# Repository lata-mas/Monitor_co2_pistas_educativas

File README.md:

# Monitor de CO2 con sensores NDIR intercambiables para evaluar la ventilación natural

En este repositorio se encuentran los archivos necesarios para replicar el monitor de CO2 desarrollado en el Instituto de Energías Renovables de la UNAM, ubicado en Temixco, Morelos, México.

Los archivos para el PCB se encuentran en el folder **electric_design**. Los archivos KiCAD del esquema del PCB y el diagrama eléctrico se encuentran en el folder **pcb_src**. Los archivos para maquinar o cortar por láser el PCB se encuentran en el folder **pcb_gerber**. El diagrama eléctrico en formato PDF se encuentra en el folder **pcb_pdf**. Las plantillas para producir el PCB por impresión de pantalla en formato JPG se encuentran en el folder **pcb_jpg**. Adicionalmente, renders tridimensionales del PCB con las partes del monitor se encuentran en el folder **pcb_view3D**. Los archivos para producir la carcasa del monitor de CO2 se encuentran en el folder **hardcase_pdf**. Los archivos FreeCAD se encuentran en el folder **cad**, junto con archivos en PDF para calcar en el folder **hardcase_pdf**, y también archivos en formato STL y DXF en el folder **hardcase_printable**.

El programa, código fuente y binario, se encuentran en el folder **software**. En el folder **notebook** se encuentran libretas de Jupyter con los datos de la calibración hecha y la campaña experimental, los datos se encuentran en el folder **dat**.

# Lista de componentes
| Designador  | Componente                      | Cantidad | Costo (MXN) | Fuente de materiales |
|-------------|---------------------------------|----------|-------------|----------------------|
| ESP8266     | NodeMCU V3.0 Lolin              | 1        | 159.0       | [Steren](https://www.steren.com.mx/placa-de-desarrollo-nodemcu-esp8266.html) |
| Sensor CO2  | S8LP                            | 1        | 800.0       | [Digikey](https://www.digikey.com.mx/es/products/detail/senseair/004-0-0053/10416532) |
| Sensor CO2  | SEN0220                         | 1        | 1600.0      | [DFROBOT](https://www.dfrobot.com/index.php?route=product/product&product_id=1565) |
| Sensor CO2  | SCD30                           | 1        | 1067.0      | [DigiKey](https://www.digikey.com.mx/es/products/detail/sensirion-ag/SCD30/8445334) |
| Pantalla    | Pantalla de 4 dígitos           | 1        | 112.0       | [Seeed Studio](https://www.seeedstudio.com/Grove-4-Digit-Display.html?queryID=a52cccea41a634e8bc10114075018055&objectID=1651&indexName=bazaar_retailer_products) |
| LED         | LED RGB                         | 1        | 4.3         | [Seeed Studio](https://www.seeedstudio.com/5mm-Triple-Output-LED-RGB-Common-cathode-20-PC-p-623.html?queryID=996fc5e5da5e1e2ef55538094fc749c5&objectID=1920&indexName=bazaar_retailer_products) |
| BUZZER      | Zumbador activo                 | 1        | 27.7        | [Seeed Studio](https://www.seeedstudio.com/Grove-Buzzer.html?queryID=762ee5a017832256c2a6a486656facf6&objectID=1805&indexName=bazaar_retailer_products) |
| microUSB    | Adaptador microUSB              | 1        | 7.0         | [UElectronics](https://uelectronics.com/producto/adaptador-micro-usb-tipo-b-hembra-a-dip-pcb-5-pines/) |
| Botón       | Botón pulsador                  | 1        | 27.7        | [Newark](https://www.newark.com/philmore/30-10062/product-range/dp/43W7727?st=button) |
| Batería     | Banco de energía 2500 mAh       | 1        | 200.0       | [Newark](https://www.newark.com/multicomp/mc011332/power-bank-5-2ah-5vdc/dp/94AC6834?st=power%20bank) |
| R1          | Resistencia de 10 kOhm          | 1        | 2.5         | [Newark](https://www.newark.com/arcol/mra0207-10k-b-15ppm-ta/res-10k-0-10-250mw-axial/dp/79Y4556?st=resistor%2010kohm) |
| R2          | Resistencia de 220 Ohm          | 3        | 2.5         | [Newark](https://www.newark.com/multicomp-pro/mccfr0w4j0221a50/carbon-film-resistor-220-ohm-250mw/dp/58K5029?st=resistor%20220%20ohm) |
| Grove       | Cable groove                    | 1        | 2.5         | [Seeed Studio](https://www.seeedstudio.com/Grove-Universal-4-Pin-Buckled-5cm-Cable-5-PCs-Pack.html?queryID=5db340ba008fd0a5fd1f440a6d09659c&objectID=1701&indexName=bazaar_retailer_products) |
| Terminal    | Conector vertical de 4 pines GROVE 2mm | 1  | 2.5  | [Digikey](https://www.digikey.com.mx/en/products/detail/seeed-technology-co-ltd/110990030/5482560) |
| Pines       | 40 pines hembra                 | 2        | 6.7         | [Seeed Studio](https://www.seeedstudio.com/2-54mm-pitch-pin-headers-Female-40pin-in-1-line-p-16.html?indexName=bazaar_retailer_products&objectID=2093&queryID=3d723c52f9b58905e53b48e95182a7c6) |
| Tornillos   | Tornillos M3 x 60 mm            | 4        | 5.0         | [Amazon](https://www.amazon.com.mx/gp/product/B08XB8S55X/ref=ppx_yo_dt_b_search_asin_title?ie=UTF8&th=1) |
| Tuercas     | Tuercas hexagonales M3-0.5 mm   | 4        | 1.0         | [Amazon](https://www.amazon.com.mx/gp/product/B07ZFFFRJ5/ref=ppx_yo_dt_b_search_asin_title?ie=UTF8&th=1) |
| Popote      | Popote rígido de plástico       | 2        | 3.4         | [Amazon](https://www.amazon.com.mx/Pajitas-Repuesto-Pl%C3%A1stico-Reutilizables-Pinceles/dp/B0925H4F6R/ref=sr_1_18?__mk_es_MX=%C3%85M%C3%85%C5%BD%C3%95%C3%91&crid=IM4WCLYX9S0K&keywords=popote+rigido&qid=1693848668&sprefix=popote+rigido%2Caps%2C150&sr=8-18&ufe=app_do%3Aamzn1.fos.4e545b5e-1d45-498b-8193-a253464ffa471) |
| Cable       | Cable jumper o 22-26 AWG 6 cm   | 2        | 1.8         | [Adafruit](https://www.adafruit.com/product/794) |

# Instrucciones de armado

El proceso de construcción se divide en cinco etapas. La primera etapa describe el ensamblaje del hardware para el monitor de CO2. La segunda etapa detalla la configuración y el procedimiento de carga del firmware para el ESP8266. En la tercera etapa se realiza una prueba de ensamblaje y en la cuarta etapa se lleva a cabo la configuración para la plataforma IoT. La quinta y última etapa implica el ensamblaje de la carcasa y la conexión de la batería USB si es necesario. Es importante destacar que el monitor de CO2 puede construirse y probarse en ausencia de los sensores de CO2, lo que permite adaptarse a posibles demoras en la entrega de componentes en regiones como México.

### Ensamblaje del monitor de CO2

Los siguientes pasos deben llevarse a cabo una vez que el usuario esté listo para construir el monitor de CO2, considerando que se puede probar y configurar aunque no haya un sensor de CO2 en el momento de la construcción, definiendo un sensor ficticio.

1. La PCB es de doble cara y puede producirse mediante serigrafía o mecanizado. Una de las caras tiene impresa la posición de las resistencias, sensores, led, etc., que se llamará cara frontal y el lado sin etiquetar cara trasera. Ambos lados de la PCB se muestran en la Figura 1a) cara frontal y 1b) cara trasera.
2. Soldar dos cables puente (6 cm de largo) al botón pulsador.
3. Soldar los siguientes componentes en la cara frontal. Cuatro resistencias, que están marcadas en la PCB como R1 para la resistencia de 10 $kOhm$ y R2, R3 y R4 son resistencias de 220 $Ohm$. Soldar dos líneas de quince pines hembra para el ESP8266. Soldar un conector hembra de cuatro pines para el LED. Para el botón, introducir los cables del botón en esta cara, por lo que la soldadura debería estar en la cara trasera. Insertar el conector vertical grove y soldar. En este punto, la PCB debería parecerse a la Figura 1c).
4. En la cara trasera, soldar lo siguiente: Soldar el adaptador MicroUSB y el conector hembra de tres pines para el zumbador, el conector hembra para este último debe estar doblado.
5. Si se usa S8LP, soldar dos líneas de conector hembra de seis pines en la cara trasera. En este punto, la cara trasera de la PCB debería parecerse a la Figura 1d). Luego soldar dos líneas de seis pines al sensor CO2 S8LP y enchufarlo en la PCB como se muestra en la Figura 2a).
6. Si se usa SCD30 o SEN0220, soldar una línea de conector hembra de cuatro pines en la cara trasera y, dependiendo del sensor, conectar como se muestra en la Figura 2b) para SCD30 y como se muestra en la Figura 2c) para SEN0220.
7. Enchufar el cable rojo del LED RGB apuntando al borde de la PCB en la cara frontal.
8. Enchufar la pantalla de 4 dígitos con un cable universal de cuatro pines con hebilla.
9. Enchufar el zumbador en el conector hembra de tres pines doblado.
10. Enchufar el ESP8266 con conexión microUSB alineada con el borde de la PCB.
<table>
  <tr>
    <td>
      <figure>
        
        <figcaption>a)</figcaption>
      </figure>
    </td>
    <td>
      <figure>
        
        <figcaption>b) </figcaption>
      </figure>
    </td>
  </tr>
  <tr>
    <td>
      <figure>
        
        <figcaption>c) </figcaption>
      </figure>
    </td>
    <td>
      <figure>
        
        <figcaption>d) </figcaption>
      </figure>
    </td>
  </tr>
</table>

**Figura 1**: a) Cara frontal y b) cara trasera de la PCB para el monitor de CO2 sin componentes. Tras soldar los componentes c) cara frontal y d) cara trasera de la PCB. La cara frontal tiene etiquetas para los componentes.

<table>
  <tr>
    <td style="text-align: center;">
      <figure>
        
        <figcaption>a) S8LP</figcaption>
      </figure>
    </td>
    <td style="text-align: center;">
      <figure>
        
        <figcaption>b) SCD30</figcaption>
      </figure>
    </td>
    <td style="text-align: center;">
      <figure>
        
        <figcaption>c) SEN0220</figcaption>
      </figure>
    </td>
  </tr>
</table>

<figcaption>**Figura 2**: a) S8LP, b) SCD30, y c) SEN0220 sensores conectados en la cara trasera.</figcaption>

### Configuración y carga del firmware en el ESP8266

Antes de cargar el firmware en el ESP8266, en el archivo .ino, localiza la línea `#define S8LP` y reemplaza `S8LP` con el sensor de CO2 que hayas elegido. Las opciones disponibles son `DUMMY, SEN0220` y `SCD30`. Vale la pena mencionar que la opción `DUMMY` se utiliza cuando el sensor seleccionado no está disponible. Esta opción genera datos simulados, permitiendo evaluaciones preliminares del hardware.

Adicionalmente, en las líneas donde se define:

```
#define CO2_MIN 400
#define CO2_MID 600
#define CO2_MAX 700
```

tienes la opción de configurar los colores verde, amarillo y rojo, respectivamente, que también corresponden a la alarma audible.

En el archivo `arduino_secrets.h`, los usuarios deben especificar la URL de la plataforma IoT ThingsBoard. Además, el ESP8266 establece un servicio web específico para configurar la red WiFi a la que se unirá y el token del dispositivo donde el monitor de CO2 publicará sus datos. El nombre de usuario y contraseña del administrador pueden ajustarse en este archivo o mantenerse como están.

Una vez que todos los cambios necesarios estén hechos, el archivo .ino puede cargarse en el ESP8266 usando el Arduino IDE. Cuando se configura un gran conjunto de monitores de CO2, se recomienda exportar el archivo como un archivo binario. Para hacer esto, una vez abierto el archivo .ino y compilado para verificar errores, el usuario debe ir a Sketch, Export compiled binary y el archivo binario puede cargarse en diferentes monitores de CO2. En la carpeta /software/build del repositorio se puede encontrar el archivo binario que usamos para configurar los monitores de CO2 y un script bash, `foo.sh`, como referencia para cargar el binario usando esptool.

### Prueba de ensamblaje

Al encender el Monitor de CO2, este verificará si el zumbador y el LED RGB están funcionando correctamente. Si ambos funcionan bien, el zumbador emitirá un sonido y el LED RGB mostrará los colores rojo, verde y azul antes de comenzar a funcionar.

### Configuración para la plataforma IoT

Una vez cargado el firmware en el ESP8266 y encendido por primera vez, el monitor de CO2 establece automáticamente un punto de acceso denominado `monitorCO2-XXXXXXXXX` donde las `X` se reemplazan con los últimos nueve dígitos de la dirección MAC de cada ESP8266. Para configurar el token necesario y la información de WiFi, haz lo siguiente:

1. Conéctate a la red WiFi del monitor de CO2 llamada `monitorCO2-XXXXXXXXX` desde un computador cercano.
2. Abre un navegador y navega a `http://192.168.4.1`, donde te llevará a una interfaz de configuración.
3. Inicia sesión utilizando las credenciales predeterminadas: nombre de usuario `admin` y contraseña `password`. Estos corresponden a las constantes `SECRET_WWW_USERNAME` y `SECRET_WWW_PASSWORD` en el archivo .ino del firmware. A menos que el código haya sido modificado, estas serán las credenciales predeterminadas.
4. Luego se te solicitará que ingreses los detalles de la red WiFi que el ESP8266 utilizará para conectarse a Internet junto con su contraseña, también se te pedirá el token del dispositivo.
5. Después de proporcionar esta información, el monitor de CO2 almacenará los datos y desactivará su función de punto de acceso.
6. Reinicia el ESP8266.

Si decides no completar esta configuración, el monitor de CO2 seguirá siendo completamente operativo para mediciones pero no enviará datos a la plataforma IoT y el punto de acceso estará disponible hasta que se realice la configuración.

### Carcasa para el monitor de CO2 y batería

La carcasa del Monitor de CO2 consiste en dos láminas rígidas con recortes para la pantalla, el led y para el botón. Se ensambla con cuatro tornillos, tuercas y dos popotes cortados en ocho piezas (2.5 cm cada pieza) que se utilizan como separadores. Antes de ensamblar la carcasa, el monitor de CO2 debe parecerse a lo mostrado en la Figura 3 a) la cara frontal y b) la trasera usando el S8LP. En la Figura 4 a) se muestran las láminas rígidas para la carcasa con los recortes para el sonido, ranuras, pantalla, botón, led y tornillos para el ensamblaje. La pantalla se asegura a una de las láminas rígidas usando 2 tornillos que generalmente se incluyen con la pantalla. En la misma lámina, hay un orificio donde encaja el LED, en caso de usar tableros opacos. También tiene 4 orificios por los cuales pasarán los tornillos. Esta lámina corresponde a la cara frontal de la PCB. La otra lámina de la carcasa tiene un recorte para asegurar el botón y ranuras para asegurar una ventilación adecuada para el sensor de CO2.

Finalmente, el monitor de CO2 ensamblado con láminas transparentes como carcasa y con una batería USB adjunta se muestra en la Figura 4 b).

**Figura 3**: a) Cara frontal y b) cara trasera de la PCB con todos los elementos soldados y enchufados.

**Figura 4**: a) Láminas rígidas con recortes para la carcasa, tornillos y popotes rígidos y b) Monitor de CO2 completamente ensamblado y funcionando, alimentado con una batería USB.

### Instrucciones de operación

Una vez que el monitor de CO2 está ensamblado y configurado, puede ser encendido utilizando el cable microUSB. Al activarse, el monitor comienza a medir las concentraciones de CO2, mostrando el promedio móvil de un minuto en su pantalla de 7 segmentos. Las alarmas visuales y sonoras preconfiguradas alertarán a los usuarios cuando sea necesario ventilar (indicado por una luz amarilla o dos pitidos) o si se recomienda evacuar el espacio (señalado por una luz roja y tres pitidos).

La alarma audible del Monitor de CO2 está diseñada para activarse cuando las concentraciones de CO2 alcanzan o superan las 600 ppm. Específicamente, para niveles entre 600 y 699 ppm, la alarma produce dos pulsos cada 20 segundos. Para concentraciones de 700 ppm o más, emite tres pulsos en el mismo intervalo. Esta característica auditiva es especialmente beneficiosa para usuarios con discapacidad visual que podrían tener dificultades con el sistema de colores o la lectura de la pantalla. Para desactivar temporalmente la alarma audible, presiona y mantén presionado el botón durante 20 segundos después del pitido. La alarma se reactivate una vez que las concentraciones de CO2 vuelvan al rango seguro de 400-599 ppm, asegurando alertas renovadas si los niveles exceden las 600 ppm. Si se prefiere, el zumbador puede ser excluido o desmontado del diseño sin afectar las funciones del monitor.

Los tres sensores seleccionados cuentan con un mecanismo de autocalibración que asume una exposición periódica al aire fresco (aproximadamente 400 ppm de CO2) durante la operación. Para una precisión de calibración óptima, los sensores deben experimentar exposición al aire fresco. Sin embargo, en entornos con concentraciones de CO2 consistentemente elevadas, la calibración manual puede ser más apropiada, ya que la falta prolongada de exposición a niveles ambientales puede resultar en desviaciones de calibración.

Si el Monitor de CO2 encuentra algún problema, mostrará uno de los siguientes códigos de error en su pantalla:
- F000: Imposible conectar al WiFi.
- E000: Falla en la medición del sensor de CO2.
- E001: Falla en la inicialización del sensor de CO2.
- E002: Falla en la modificación del intervalo de medición.
- E003: Falla en el comando de autocalibración.

Los mensajes de error E002 y E003 son exclusivos del sensor SCD30 y podrían aparecer durante su modo de autocalibración. Este modo puede ser activado dentro del código de Arduino a través de la función `InitSensor()`.

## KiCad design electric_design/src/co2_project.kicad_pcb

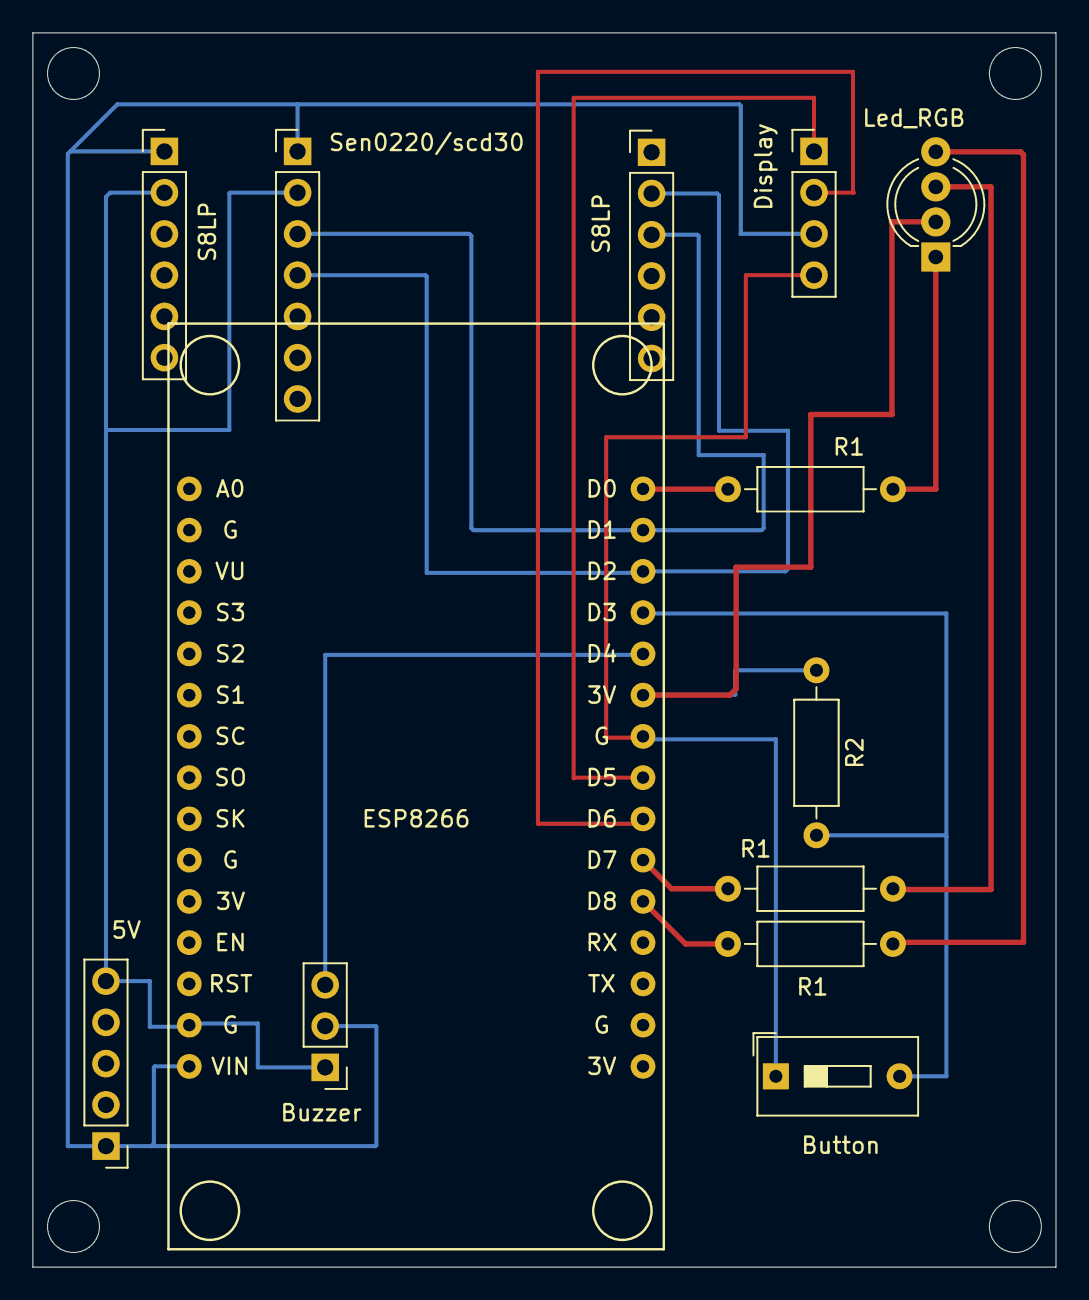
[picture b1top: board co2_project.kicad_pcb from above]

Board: 2 copper layers, 63.0 x 76.0 mm, 13 parts (0 on the bottom side), 16 nets.

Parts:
5V: 5v; PinHeader_1x05_P2.54mm_Vertical
Button: Button; SW_DIP_SPSTx01_Slide_9.78x4.72mm_W7.62mm_P2.54mm
Buzzer: Buzzer_activo; PinHeader_1x03_P2.54mm_Vertical
Display: Display; PinHeader_1x04_P2.54mm_Vertical
ESP8266: NodeMCU_1.0_(ESP-12E); NodeMCU-LoLinV3
Led_RGB: LED_RGB; LED_D5.0mm-4_RGB_Wide_Pins
R1, R1#2, R1#3: 220; R_Axial_DIN0207_L6.3mm_D2.5mm_P10.16mm_Horizontal
R2: 10k; R_Axial_DIN0207_L6.3mm_D2.5mm_P10.16mm_Horizontal
S8LP: s8; PinHeader_1x06_P2.54mm_Vertical
S8LP#2: lp; PinHeader_1x06_P2.54mm_Vertical
Sen0220/scd30: sen0220_scd30; PinHeader_1x07_P2.54mm_Vertical

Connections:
unnamed: Led_RGB.1, R1#3.2
unnamed: ESP8266.25, Led_RGB.2, R2.1
unnamed: Led_RGB.3, R1#2.2
unnamed: Led_RGB.4, R1.2
unnamed: 5V.1, Buzzer.2, Display.3, ESP8266.15, S8LP#2.1, Sen0220/scd30.1
unnamed: 5V.5, Buzzer.1, ESP8266.14, S8LP#2.2, Sen0220/scd30.2
unnamed: ESP8266.20, R1.1
unnamed: ESP8266.21, R1#2.1
unnamed: ESP8266.30, R1#3.1
unnamed: Button.2, ESP8266.27, R2.2
unnamed: Button.1, Display.4, ESP8266.24
unnamed: Buzzer.3, ESP8266.26
unnamed: Display.2, ESP8266.22
unnamed: Display.1, ESP8266.23
unnamed: ESP8266.28, S8LP.2, Sen0220/scd30.4
unnamed: ESP8266.29, S8LP.3, Sen0220/scd30.3

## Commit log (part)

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2021-06-25 detalles
2021-06-25 integracion de seaborn
2021-06-25 integracion de seaborn y correcciones de estilo
2021-06-25 boxplot showmean=true
2021-06-29 mensaje
2021-06-30 actualizacion prueba 002
2021-06-30 agregue datos de sensores thingsboard
2021-06-30 agregue nuevamente datos de sensores thingsboard
2021-07-01 prueba de concentraciones
2021-07-04 respaldo
2021-07-05 Add files via upload
    agregue datos del fluke prueba fin de semana
2021-07-06 agregue datos fluke prueba ventilador
2021-07-06 actualiza
2021-07-07 caja hermetica con ventilador
2021-07-07 Universal Shield v1.1
    Damn! SEN0220 connects RX with RX and TX with TX, instead of common
    sense UART connections RX-TX / TX-RX.
    SEN0220 is used as reference sensor, so changed to match SEN0220
    connector.
    Other UART sensor must follow RX-TX / TX-RX convention.
2021-07-07 Universal Code for Arduino Uno WiFi Rev. 2
    Just define your sensor with:
    Supported sensors:
    * DUMMY (test purposes)
    * SEN0219 (deprecated)
    * MH_Z14A
    * SEN0220
2021-07-07 Added POST_INTERVAL_MS
    Defines the post interval in milliseconds to MQTT broker.
    Default: one read/post every 60 seconds.
2021-07-08 Fixed mistaken CREDENTIALS in arduino_secrets.h
    Vaya, por fin regresó el iZZi. Corrigiendo las CREDENCIALES
    de acceso al thingsboard.
2021-07-12 Added suport for scd30. Thank you very much, Lady Ada.
    There is a library from AdaFruit for sensor scd30.
2021-07-16 Added support for ESP32 based dev boards
    Compiled for Adafruit ESP32 Feather and LOLIN ESP32 dev board
2021-07-19 documentacion scd30
2021-07-21 pruebas con scd30
2021-07-22 repo
2021-07-23 agruegue datos Fluke de la prueba 700 y 800 ppm
2021-07-23 primer resultado scd30
2021-07-24 Added co2scd30 +WiFi +(oled|epd) +lowpower
    For Arduino MKR1000, MKR1010 and Nano33 IoT
    Supports SSD1306 128x64 mono OLED
    Preliminary support for SSD1681 200x200 mono EPD
2021-07-26 agregue nuevamente pruebas del dia 23/07/2021
2021-07-26 analisis funciones
2021-07-26 libreta automatizada concentraciones
2021-07-27 co2 520, 625, 750, 800 ppm
2021-07-27 update imac
2021-07-27 actualiza orden
2021-07-27 normalizar libretas
2021-07-28 integrar resultados
2021-07-28 resultados, observaciones
2021-07-30 imagen
2021-07-30 tabla
2021-07-30 tabla formateada
2021-07-30 referencias
2021-07-30 sensores
2021-07-30 contenido
2021-07-30 agregue datos del fluke y disp nuevos prueba 800
2021-08-04 libreta induccion
2021-08-04 documentacion
2021-08-05 Preliminar WiFi recovery method
    Try to recover WiFi connection when POST statuscode != 200
    If connection can't be recovered, starting waiting one second.
    Every iteration doubles the wait time, until 128 seconds. Then
    restart with one second wait until connection is recovered.
    Builtin LED flashes fast while waiting for WiFi connection.
    No sensor data is read while recovering connection.
2021-08-05 No keep waiting for WiFi recovery but display sensor value
    Modified: not wait wifi connection, try once and return.
    Read/Display sensor, then try to POST to network, if
    statuscode != 200 try once reconnect WiFi.
2021-08-05 Added ESP8266 pin layout
    Default pinout for UART(13,15) & I2C(4,5), no need to rewrite code
    Display(CLK/DIO)=(12,14) moved from(6,7)
2021-08-05 Sensor scd30 with 128x64 OLED display
    Updated latest WiFi recovery method from co2-all-sensors
    Added IER-UNAM splash screen
2021-08-05 The sandbox
    Added splash.h
    Added sandbox, por si quieren compartir algo, eventualmente se borrará}
    del repositorio cuando una vez que esté terminado.
2021-08-05 Fixed list of sensors
    Just fixed list of sensors to include:
    * DUMMY
    * SEN0219
    * SEN0220
    * MH-Z14A
    * T3022
2021-08-05 Documentation for every sensor tested so far now
    PDF documentation from manufacturers:
    * SEN0219 aka Winsen MH-Z14A
    * SEN0220 aka Winsen MH-Z16
    * T3022 aka Telaire T67xx
    * S8LP aka Sensair S8 Low Power
    * SCD30 aka Sensirion SCD30 Sensor Module
2021-08-06 Added support for 8-bits AVR ATmega32u4 boards
    Tested with Arduino Leonardo. It should work with Arduino Micro
    and other 32u4 boards with Serial1
2021-08-07 Probando las capacidades del ESP8266
    Simple "multi-tasking" program
2021-08-08 Preliminar: soporte para el scd30
    Algoritmo loop()
    Si hay datos disponibles del sensor
    Leer Sensor
    Mostrar co2ppm en pantalla de segmentos
    Si es tiempo de postear
    Preparar payload
2021-08-08 Ticker library para crear dos cauces
    Se intentó utilizar la biblioteca Ticker para crear dos cauces:
    1 cauce para leer el sensor cada 2 segundos
    2 cauce para postear al thingsboard
    El programa revienta cuando trata de postear y aún no está establecida
    la comunicación. En realidad, nunca pudo establecer la comunicación, así
    que siempre reventó.
2021-08-09 s/ArduinoHttpClient/ESP8266HTTPClient/
    Se cambió la biblioteca ArduinoHttpClient por ESP8266HTTPClient
    Aunque ya no revienta, sigue sin postear, error=-1:connection
    failed
    ¿Será que no le gusta postear dentro del ticker?
2021-08-09 Preliminar servidor de web para configuración en línea
    Aún no decidimos si va a ser necesario hacer una configuración en línea
    pero por lo pronto tiene un servidor de dos páginas, que en realidad no
    hace gran cosa-.
2021-08-10 Prueba final del ticker: con soporte para los tres sensores
    Esta versión funciona lo suficientemente bien como para promoverla
    al directorio sketchbook con nombre (final) monitorCO2.ino
2021-08-10 monitorCO2: primera versión
    Optimizada con las bibliotecas especializadas para el ESP8266
    Utiliza la biblioteca Ticker para el control de la lectura de datos
    y para el POST en el thingsboard
    Soporta los sensores: sen0220, s8lp y scd30
    Soporte preliminar para servidor de web, con autentificación básica
    (usuario/contraseña) para configuración en línea.
2021-08-10 agregue scr s8lp con codigo de rgb y buzzer
2021-08-10 Algunos ajustes menores
    Utilizando como período de lectura MEASUREMENT_INTERVAL*1024ms
2021-08-10 D1/D2 (5/4) para I2C y para SoftwareSerial
    Esto nos deja libres los pines 12-15 para el LED RGB y para el Zumbador.
    Y tal vez reutilizar el botón FLASH en el pin 0
2021-08-10 agregue pin layout jpg
2021-08-10 monitorCO2 pin reference 2021-08-10-000
    Primera revisión del monitorCO2 con la referencia de pines del
    2021-08-10-001
    Creo que hay un conflicto con LED_BUILTIN y BUZZER
    En todo este tiempo LED_BUILTIN parpadea rápidamente si hay algún
    problema, y lentamente en operación normal.
2021-08-10 Ultima versión con LED_BUILDIN como testigo de operación.
    No modo: no alcanzan los pines. A quitar el uso del LED_BUILTIN como
    testigo de operación.
2021-08-10 Prueba del Buzzer con la biblioteca Ticker
    Para no bloquear el monitorCO2 con delays
2021-08-10 Se ha eliminado el uso del LED_BUILTIN como testigo de operación
    En algunos lugares he agregado mostrar los códigos de error en el
    display
2021-08-11 Fixed chkwifi() report on display
    Faster report chkwifi() on display
2021-08-11 chkwifi() now reports WiFi.status() on display
    From wl_definitions.h
    0xf000 WL_IDLE_STATUS
    0xf001 WL_NO_SSID_AVAIL
    0xf002 WL_SCAN_COMPLETED
    0xf003 WL_CONNECTED
    0xf004 WL_CONNECT_FAILED
2021-08-11 co2ppm = cma.avg()
    Unificando el valor co2ppm al promedio, se utiliza para el display,
    el semáforo, la alarma y el POST.
2021-08-11 Added cma.h & cma.cpp
    I forgot to add these files
2021-08-12 Added CurieEddystoneURL
    Eddystone(TM) URL permite publicar un URL en el sistema BLE.
    Un teléfono inteligente puede detectar la baliza y abrir el URL.
2021-08-12 agregue esquematico y vista proto de ESP8266_CO2
2021-08-12 agregue correción del esquematico
2021-08-12 co2_fritzing
2021-08-12 agregue correcion de esquematico CO2
2021-08-13 hize una pequeña correcion en el esquematico
2021-08-13 test-eeprom
    Un poco más complicado de lo que yo esperaba, pero ya se puede
    escribir/leer datos a la EEPROM
    Aunque de momento tal parece que sólo necesitamos el ACCESS_TOKEN
    de una vez aproveché para agregar WIFI_SSID y WIFI_PASS
2021-08-13 agregue correcion de esquematico
2021-08-18 agregue archivos gerber y fritzing del pcb
2021-08-21 Prueba de concepto WIFI-AP -> WIFI-STA
    Si el EEPROM está vacío arranca como ACCESS_POINT con SSID=monitorCO2-MAC-ADDRESS
    Si el EEPROM tiene datos los utiliza para conectarse a la red indicada
    Se configura un WebServer con tres URI iniciales:
    / RootPage: debe presentar un formulario pidiendo los datos y apuntando a /commit
    /commit recibe el formulario, copia los datos y escribe la EEPROM
    /clear sirve para borrar la EEPROM mientras hacemos pruebas
2021-08-21 Intento de poner un BEACON con el URL del Sensor, pero no sirve sin instalar una apĺicación
    Aunque el BEACON funciona, requiere instalar una aplicación, así que realmente no es muy útil para el usuario final.
    En su lugar, el método WIFI-AP -> WIFI_STA es mucho más sencillo para inicializar los dispositivos.
2021-08-21 BASIC HTML POST FORM / COMMIT
    Simple página Web con un formulario POST y una entrada de datos: ACCESS_TOKEN
    Simple página web para el commit que graba los datos a la EEPROM
    Sigue el URI /reset para borrar la EEPROM mientras se hacen las pruebas
    Ya se puede copiar al programa principal, pero ya tengo sueño
2021-08-25 More WiFi optimizations
    Using ESP8266 specific functions: isConnected() and reconnect() to
    improve WiFi roaming connection
2021-08-25 More testing WIFI_AP <-> WIFI_STA
    Playing with WIFI_AP -> WIFI_STA
2021-08-25 agregue gerber con espacio correcto para ESP v3
2021-08-26 quite perforaciones de display anterior de pcb
2021-08-30 reacomode las perforaciones de las esquinas
2021-08-31 gire posicion de buzzer por motivos de la carcasa
2021-08-31 agregue las 6 caras de la carcasa en STL
2021-09-02 Added SECRET credentials
    You need SECRET credential to do /reset (erase eeprom)
2021-09-02 POST/EEPROM/WiFi/AP/STA behavior
    Promoted sandbox/test-wifi-ap operations to main program:
    1) Empty EEPROM puts monitorCO2 into AccessPoint mode
    join to network and point to http://192.168.4.1/
    to fill in the blanks
    2) Submit form and after response reset monitorCO2
    3) Now monitorCO2 reads data from EEPROM and starts station mode
2021-09-04 Added reset on MAX_READ_ERRORS. Commented CMA.
    CMA is commented.
    Added reset on MAX_READ_ERRORS
2021-09-10 agregue datos de prueba de 420 7 600 ppm
2021-09-13 agregue datos fluke pruebas 13/09/2021
2021-09-14 agregue datos de geotermia prueba del 13/09/2021
2021-09-14 agregue datos de TB de pruebas del dia 13/09/2021
2021-09-15 historicoss
2021-09-20 Reset after MAX_WIFI_ERRORS=8
    Also added CO2_MIN=400, CO2_MID=600 and CO2_MAX=800
2021-09-20 Fixed misplaced static readErrors
    12e7c3b194e58aec6e767c8ab71174a5
2021-09-23 agregue datos del fluke de pruebas de hoy 23/09
2021-09-23 BUILD 2021-09-23 12:14:15
    El binario grabado masivamente en la primera tanda de ESP8266
2021-09-23 foo.sh: script para grabar masivamente
    Un simple shell en /bin/bash para grabar los ESP8266 uno tras otro.
2021-09-24 agregue datos fluke prueba noche del 23-24 Sept
2021-09-24 carpetas
2021-09-24 libretas
2021-09-24 readme
2021-09-28 agregue archivos gerber y editable del PCB
2021-09-28 update structrure
2021-09-28 update structure
2021-09-29 agregue datos fluke de la prueba de 900 ppm 28/sep
2021-10-07 agregue archivos actualizados
2021-10-07 calibracion
2021-10-08 agregue esquematico hecho en KiCad
2021-10-12 agregue esquematico CO2
2021-10-12 agregue editables de esquematico y PCB en KiCad
2021-10-12 agregue archivos gerber KiCad
2021-10-12 organizar
2021-10-14 detalles finos
2021-10-15 nombres
2021-10-15 agregué archivos .DXF
2021-10-26 agregue vistas 3D de PCB
2021-10-28 grafica experimento
2021-10-29 pilot case
2021-10-29 format figure
2021-11-16 agregue datos de fluke de la prueba 3-7/Nov/2021
2021-11-19 Added Mute Alarm with Button_0
    Somewhere over the rainbow we miss the code, but let's write it again.
2021-11-19 Fixed mute alarm
2021-11-23 agregue codigo actualizado
2021-11-24 Synced with latest build
2021-11-24 Synced with latest build
    Added missed .h .cpp files
2022-03-24 correccion apallido
2022-04-01 agregue pcb pistas en formato PDF
2022-06-28 update figures
2022-08-10 update macos
2022-08-11 alistando
2022-08-11 libreta
2022-08-11 udate files
2022-08-11 update files
2022-08-11 gitignore
2022-08-11 removig ds_store
2022-08-12 update final
2022-08-12 zenodo json fix
2022-08-12 sin json
2022-08-12 update cleaning notebooks
2023-09-04 cambio de nombres
2023-09-05 citation
2023-09-05 update de citation
2023-09-05 json
2024-07-20 formato
